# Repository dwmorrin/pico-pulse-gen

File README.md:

# Pico Pulse Generator

Using the Raspberry Pi Pico microcontroller to produce programmable pulses, suitable for
modular synthesizers.

- 8 programmable steps (expandable)
- 3 programmed outputs (expandable)
- clock output
- internal tempo control via analog pot
- read/write mode to transfer patterns between outputs
  - write mode transfers from the 8 programming buttons to the selected output
  - read mode transfers from the selected output to the 8 programming buttons

Adds rhythmic variation to any module that takes a gate/trigger/clock input.

The multiple, synchronized outputs make simple drum programming easy.

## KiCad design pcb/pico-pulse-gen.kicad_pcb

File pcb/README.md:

thanks to [ncarandini/KiCad-PR-Pico](https://github.com/ncarandini/KiCad-RP-Pico/) for the KiCad pico files.

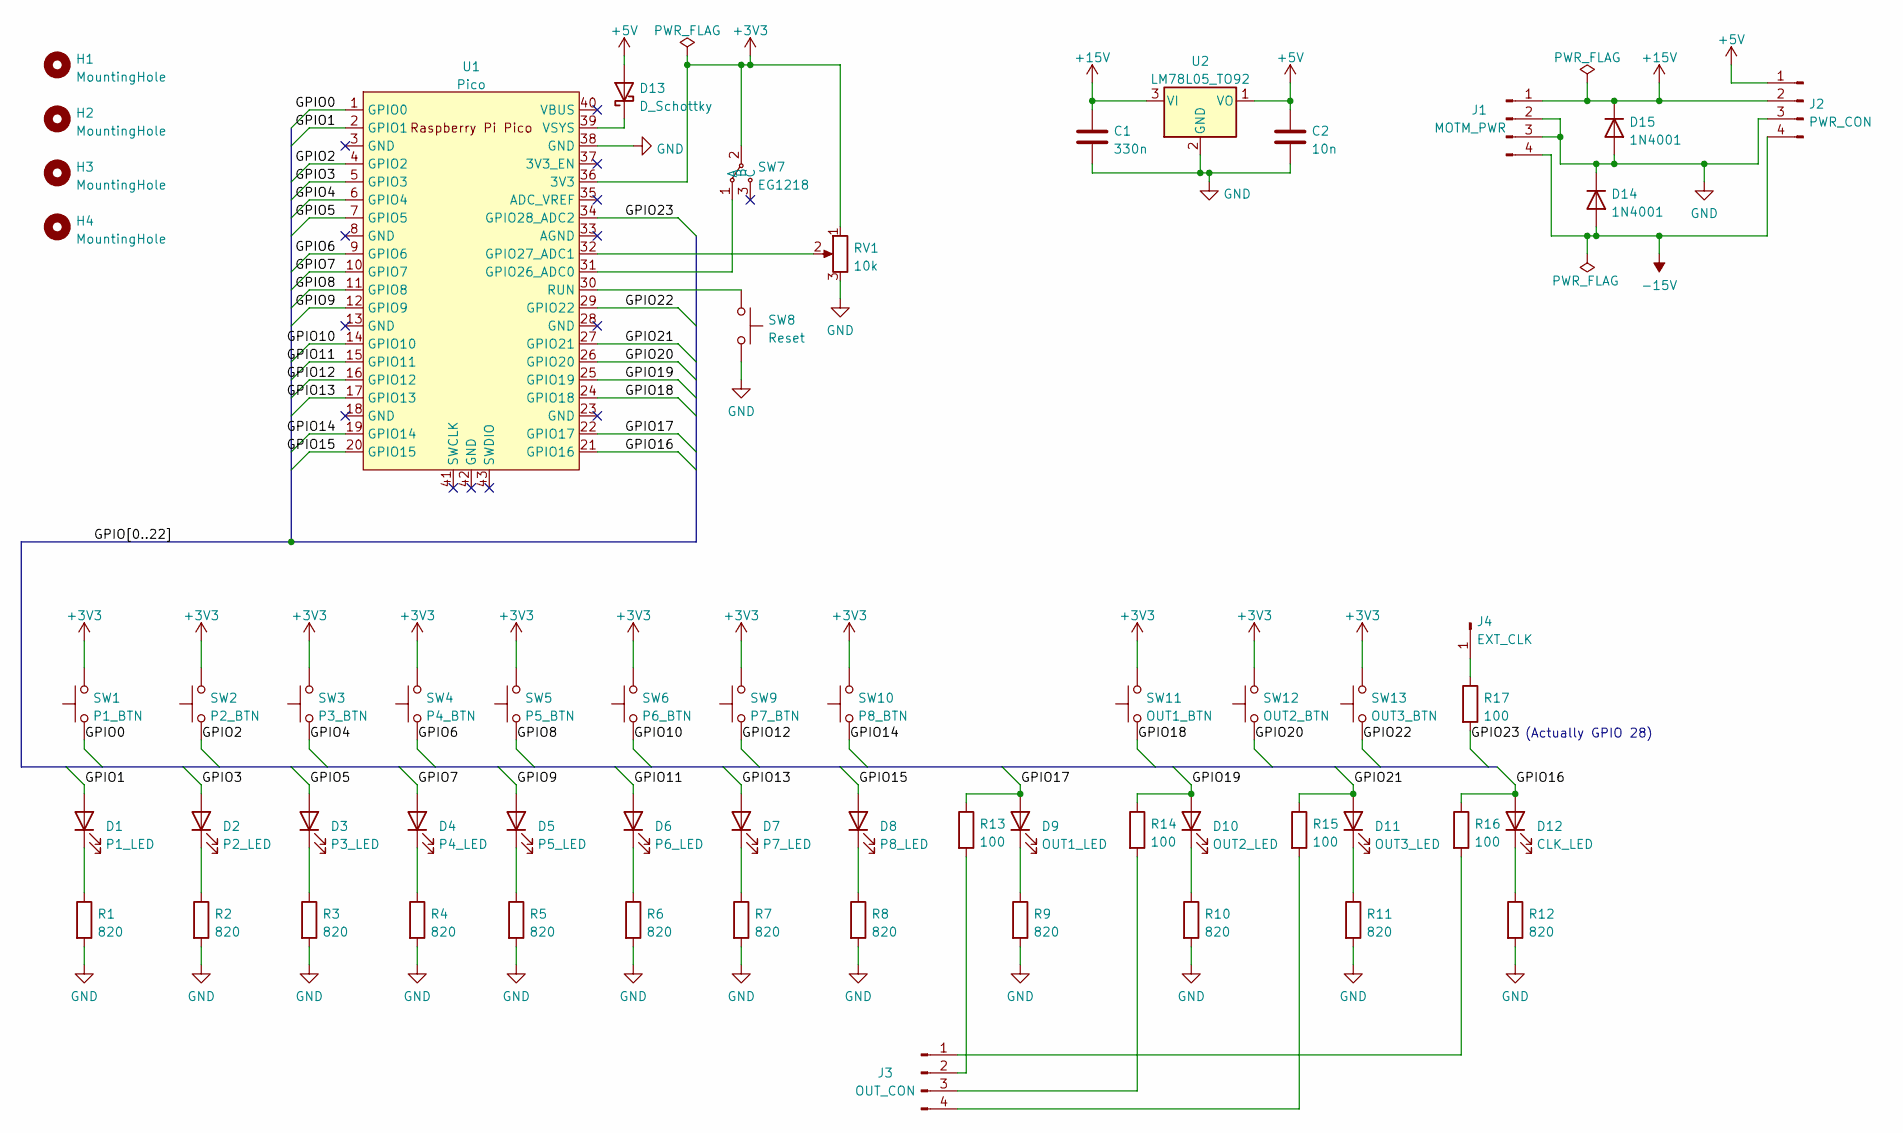
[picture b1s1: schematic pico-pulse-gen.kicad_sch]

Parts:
C1: 330n; C_Disc_D3.8mm_W2.6mm_P2.50mm
C2: 10n; C_Disc_D3.8mm_W2.6mm_P2.50mm
D1: P1_LED; LED_D3.0mm
D2: P2_LED; LED_D3.0mm
D3: P3_LED; LED_D3.0mm
D4: P4_LED; LED_D3.0mm
D5: P5_LED; LED_D3.0mm
D6: P6_LED; LED_D3.0mm
D7: P7_LED; LED_D3.0mm
D8: P8_LED; LED_D3.0mm
D9: OUT1_LED; LED_D3.0mm
D10: OUT2_LED; LED_D3.0mm
D11: OUT3_LED; LED_D3.0mm
D12: CLK_LED; LED_D3.0mm
D13: D_Schottky; D_DO-34_SOD68_P7.62mm_Horizontal
D14, D15: 1N4001; D_DO-34_SOD68_P7.62mm_Horizontal
H1, H2, H3, H4: MountingHole; MountingHole_2.7mm_M2.5
J1: MOTM_PWR; connector_motm
J2: PWR_CON; PinHeader_1x04_P2.54mm_Vertical
J3: OUT_CON; PinHeader_1x04_P2.54mm_Vertical
J4: EXT_CLK; PinHeader_1x01_P2.54mm_Vertical
R1, R2, R3, R4, R5, R6, R7, R8, R9, R10, R11, R12: 820; R_Axial_DIN0207_L6.3mm_D2.5mm_P7.62mm_Horizontal
R13, R14, R15, R16, R17: 100; R_Axial_DIN0207_L6.3mm_D2.5mm_P7.62mm_Horizontal
RV1: 10k; Potentiometer_Bourns_PTV09A-1_Single_Vertical
SW1: P1_BTN; SW_PUSH_6mm
SW2: P2_BTN; SW_PUSH_6mm
SW3: P3_BTN; SW_PUSH_6mm
SW4: P4_BTN; SW_PUSH_6mm
SW5: P5_BTN; SW_PUSH_6mm
SW6: P6_BTN; SW_PUSH_6mm
SW7: EG1218; slide_switch_e61218
SW8: Reset; SW_PUSH_6mm
SW9: P7_BTN; SW_PUSH_6mm
SW10: P8_BTN; SW_PUSH_6mm
SW11: OUT1_BTN; SW_PUSH_6mm
SW12: OUT2_BTN; SW_PUSH_6mm
SW13: OUT3_BTN; SW_PUSH_6mm
U1: Pico; RPi_Pico_SMD_TH
U2: LM78L05_TO92; TO-92_Inline

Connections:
+3V3: RV1.1, SW1.2, SW2.2, SW3.2, SW4.2, SW5.2, SW6.2, SW7.2 (B), SW9.2, SW10.2, SW11.2, SW12.2, SW13.2, U1.36 (3V3)
+5V: C2.1, D13.2 (A), J2.1, U2.1 (VO)
+15V: C1.1, D15.1 (K), J1.1, J2.2, U2.3 (VI)
-15V: D14.2 (A), J1.4, J2.4
/GPIO0: SW1.1, U1.1 (GPIO0)
/GPIO1: D1.2 (A), U1.2 (GPIO1)
/GPIO2: SW2.1, U1.4 (GPIO2)
/GPIO3: D2.2 (A), U1.5 (GPIO3)
/GPIO4: SW3.1, U1.6 (GPIO4)
/GPIO5: D3.2 (A), U1.7 (GPIO5)
/GPIO6: SW4.1, U1.9 (GPIO6)
/GPIO7: D4.2 (A), U1.10 (GPIO7)
/GPIO8: SW5.1, U1.11 (GPIO8)
/GPIO9: D5.2 (A), U1.12 (GPIO9)
/GPIO10: SW6.1, U1.14 (GPIO10)
/GPIO11: D6.2 (A), U1.15 (GPIO11)
/GPIO12: SW9.1, U1.16 (GPIO12)
/GPIO13: D7.2 (A), U1.17 (GPIO13)
/GPIO14: SW10.1, U1.19 (GPIO14)
/GPIO15: D8.2 (A), U1.20 (GPIO15)
/GPIO16: D12.2 (A), R16.1, U1.21 (GPIO16)
/GPIO17: D9.2 (A), R13.1, U1.22 (GPIO17)
/GPIO18: SW11.1, U1.24 (GPIO18)
/GPIO19: D10.2 (A), R14.1, U1.25 (GPIO19)
/GPIO20: SW12.1, U1.26 (GPIO20)
/GPIO21: D11.2 (A), R15.1, U1.27 (GPIO21)
/GPIO22: SW13.1, U1.29 (GPIO22)
/GPIO23: R17.2, U1.34 (GPIO28_ADC2)
GND: C1.2, C2.2, D14.1 (K), D15.2 (A), J1.2, J1.3, J2.3, R1.2, R2.2, R3.2, R4.2, R5.2, R6.2, R7.2, R8.2, R9.2, R10.2, R11.2, R12.2, RV1.3, SW8.2, U1.38 (GND), U2.2 (GND)
unnamed: D1.1 (K), R1.1
unnamed: D2.1 (K), R2.1
unnamed: D3.1 (K), R3.1
unnamed: D4.1 (K), R4.1
unnamed: D5.1 (K), R5.1
unnamed: D6.1 (K), R6.1
unnamed: D7.1 (K), R7.1
unnamed: D8.1 (K), R8.1
unnamed: D9.1 (K), R9.1
unnamed: D10.1 (K), R10.1
unnamed: D11.1 (K), R11.1
unnamed: D12.1 (K), R12.1
unnamed: D13.1 (K), U1.39 (VSYS)
unnamed: J3.1, R16.2
unnamed: J3.2, R13.2
unnamed: J3.3, R14.2
unnamed: J3.4, R15.2
unnamed: J4.1, R17.1
unnamed: RV1.2, U1.32 (GPIO27_ADC1)
unnamed: SW7.1 (A), U1.31 (GPIO26_ADC0)
unnamed: SW8.1, U1.30 (RUN)

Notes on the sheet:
(Actually GPIO 28)

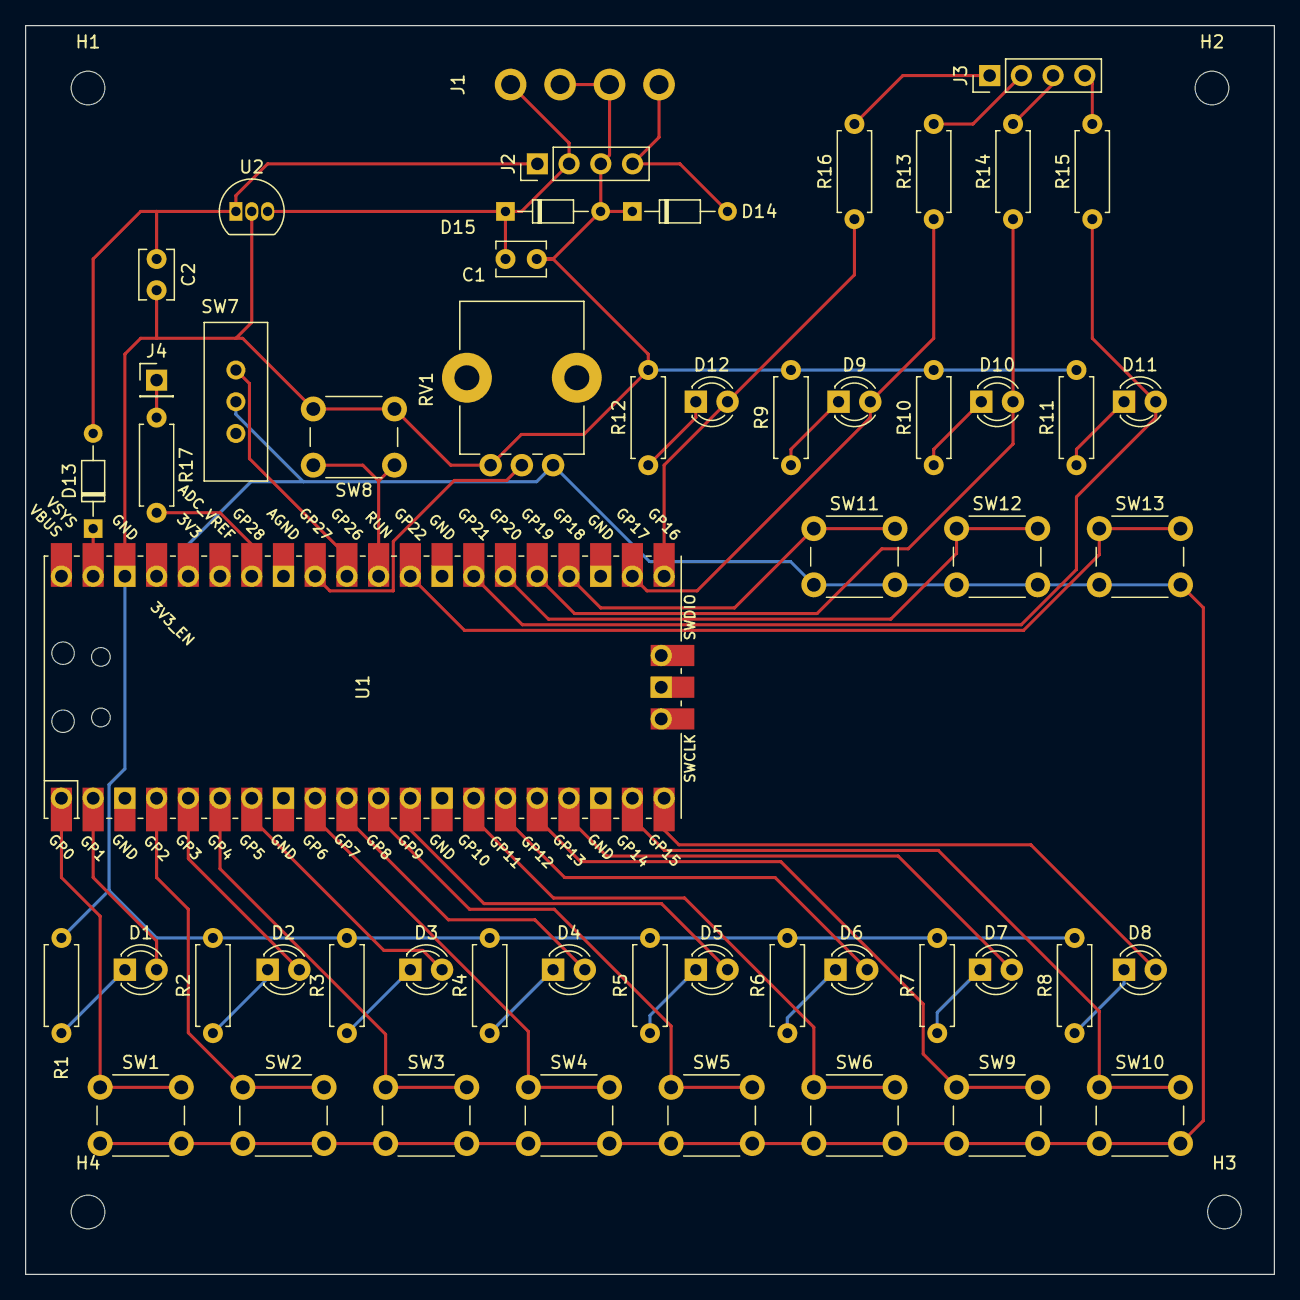
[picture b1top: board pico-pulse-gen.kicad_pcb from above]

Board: 2 copper layers, 100.0 x 100.0 mm, 58 parts (0 on the bottom side), 50 nets.

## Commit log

2021-12-27 feat: toggle buttons and blink
2021-12-27 feat: programmable pattern
2022-01-08 feat: 3 programmable patterns
    adds read/write button to recall stored patterns
    fix: ignores .DS_Store
2022-01-08 feat: adds adc for tempo ctrl
2022-01-08 feat: adds README
2022-07-10 feat: adds pcb design
2022-07-12 wip: pcb layout
2022-07-12 feat: routed pcb
